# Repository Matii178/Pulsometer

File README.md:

# Pulsometer

## Schematic
### Parts of schematic were designed based on NXP "Pulse Oximeter Fundamentals and Design" by Santiago Lopez. Link below.

https://www.nxp.com/docs/en/application-note/AN4327.pdf

KiCad full scale electronic scheme. Below I will describe each part and its function.

### Part_1: Power supply

* U1 - TL071 : Is a core of this part, its aim is to create virtual ground equal to 0.5 of Vcc.
* R1, R2 - Same values of these resistors to create 0.5 of Vcc. 
* C1, C2 - Same values, ensure stability of virtual gnd.
* H8, H9 - Inputs for external power supply.

### Part_2 Signal receiver with custom amplification

* H1, H2 - Connections for external red LED
* H3, H4 - Connections for external photodiode. It needs to be reverse biased.
* R4 - Thanks to current created by photodiode it enables 'interchanging' current to voltage. (Simple Ohm law)
* C3, R5 - It creates high-pass filter, eliminating frequencies below 0.53 Hz (approx. 32 heartbeats per minute). C3 is important to eliminate offset of signal, and R5 is used to discharge C3.
* U2A - TLC272 : Voltage follower. Used to eliminate influence of high resistance R5 on op-amp input due to its strong amplification.
* U2B - TLC272 : Non-inverting amplifier with custom amplification due to potentiometer.
* R6, R7, RV1 - Used with U2B TLC272 as parts of non-inverting aplifier. Enables to amplify signal 39-122 times.

### Part_3 Filters section

* R8, C4 - Low-pass filter, cuts off frequencies above 5.3 Hz.
* R9, R10, R11, C5, C6, C7 - Notch filter, eliminates 50 Hz frequency influence.
* C8, R12 - High-pass filter, cuts off frequencies below 0.5 Hz.

You may notice, that filter section is a filter with bandwidth starting from 0.5 Hz and ending on 5.3 Hz.
When converted to bpm, it heart rate signal starting from 32 - 318 bpm. Which is even more than enough for our purpouse.

### Part_4 output

* U3A - TLC272: Voltage follower, just as previously mentioned with U2A.
* U3B - TLC272: Non-inverting amplifier. Evens losses originating form filter section.
* R13, R14 - Parts of non-inverting amplifier U3B.
* R15, C9 - Once again low-pass filter (eliminates frequencies above 8 Hz), and also stabilizer for future ADC measurements.
* JP1, R16, R17 - Jumper with voltage divider, its aim is to ensure that even if device is powered with 5 V, it still can be connected to STM32 (ADC only supports maximal value of 3.3 V)

### PCB board layout

Visualisation of my pcb board was created using KiCad 7.0. The front and bottom parts are visible below.
Size of the board is: 6.3 x 4.1 cm.

### Photo of assembled device 

I have ordered ready to solder boards from China, but unfortunatelly I would have to wait more than one month for them, so I decided to etch them on my own. 
It is one-sided board, with 'bottom' traces created with external wires (yellow ones).

### Real life experiment

In the end I have powered my pulsometer with 3.3V (So it is compatible with STM32). I have not soldered the jumper, and I have directly connected the ouputs to oscilloscope.
Below you can see the analogue signal of my pulse. To make sure it works, I have also measured my pulse with another method (simple metronome) to compare the results. It was pretty the same :)

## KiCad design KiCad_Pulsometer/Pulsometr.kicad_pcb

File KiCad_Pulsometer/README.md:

# KiCad Project

As mentioned on a front page, here you can find electronic scheme and PCB board design.

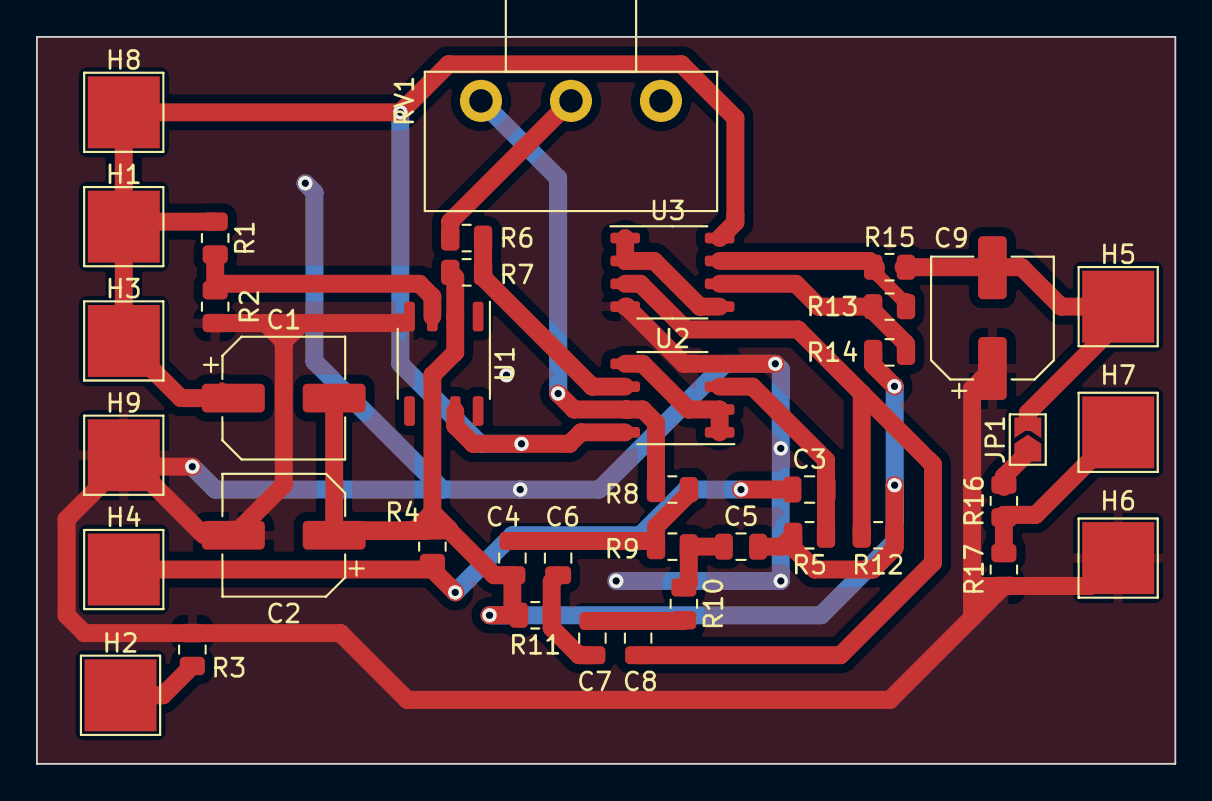
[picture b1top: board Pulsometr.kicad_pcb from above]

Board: 2 copper layers, 63.2 x 40.4 mm, 40 parts (0 on the bottom side), 22 nets.

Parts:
C1, C2, C9: 10uF; CP_Elec_6.3x5.2
C3, C5, C8: 2uF; C_0805_2012Metric
C4, C6, C7: 1uF; C_0805_2012Metric
H1, H2: RED_LED; TestPoint_Pad_4.0x4.0mm
H3, H4: Photodiode; TestPoint_Pad_4.0x4.0mm
H5: Output; TestPoint_Pad_4.0x4.0mm
H6: Gnd; TestPoint_Pad_4.0x4.0mm
H7: Output_2; TestPoint_Pad_4.0x4.0mm
H8: +5V; TestPoint_Pad_4.0x4.0mm
H9: 0V; TestPoint_Pad_4.0x4.0mm
JP1: SolderJumper_2_Open; SolderJumper-2_P1.3mm_Open_TrianglePad1.0x1.5mm
R1, R2: 47kR; R_0805_2012Metric
R3: 100R; R_0805_2012Metric
R4: 220kR; R_0805_2012Metric
R5, R12: 150kR; R_0805_2012Metric
R6: 75kR; R_0805_2012Metric
R7: 1,2kR; R_0805_2012Metric
R8, R13: 30kR; R_0805_2012Metric
R9, R10: 3.3kR; R_0805_2012Metric
R11: 1.5kR; R_0805_2012Metric
R14: 1.2kR; R_0805_2012Metric
R15, R16: 2kR; R_0805_2012Metric
R17: 1kR; R_0805_2012Metric
RV1: 100k; Potentiometer_Piher_T-16H_Single_Horizontal
U1: TL071; SOP-8_3.9x4.9mm_P1.27mm
U2, U3: TLC272; SOP-8_3.9x4.9mm_P1.27mm

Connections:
Filters: R8.1, RV1.3, U2.7
unnamed: C3.1, H4.1, R4.1
unnamed: C4.1, C6.2, R8.2, R9.1
unnamed: C5.1, R9.2, R10.1
unnamed: C6.1, C7.1, R11.1
unnamed: C7.2, C8.1, R10.2
unnamed: H2.1, R3.1
unnamed: H7.1, R16.1, R17.2
unnamed: JP1.1 (A), R16.2
unnamed: C9.2, H5.1, JP1.2 (B), R15.2
unnamed: R6.2, RV1.2
unnamed: R13.2, R15.1, U3.7
unnamed: R1.2, R2.1, U1.3 (+)
unnamed: C3.2, R5.1, U2.3 (+)
unnamed: U2.1, U2.2 (-), U2.5 (+)
unnamed: R6.1, R7.1, U2.6 (-)
unnamed: U3.1, U3.2 (-), U3.5 (+)
unnamed: R13.1, R14.2, U3.6 (-)
Virtual_gnd: C1.2, C2.1, C4.2, C5.2, R4.2, R5.2, R7.2, R11.2, R12.1, R14.1, U1.2 (-), U1.6
minus: C2.2, C9.1, H6.1, H9.1, R2.2, R3.2, R17.1, U1.4 (V-), U2.4 (V-), U3.4 (V-)
plus: C1.1, H1.1, H3.1, H8.1, R1.1, U1.7 (V+), U2.8 (V+), U3.8 (V+)
stabilizer: C8.2, R12.2, U3.3 (+)

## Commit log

2024-06-23 Included schematic and pcb design
2024-07-01 added stm32 program to measure heart bpm
2024-07-01 added Readme.md file
2024-07-02 added heart rate counter that prints and displays value in bpm
2024-07-29 new approach using Zephyr RTOS
2024-07-31 added new threads and queue to communicate
2024-08-01 added new timer, circular buffer and revamped some parts of code
2024-08-03 calculation of bpm added, new timer and added comments
